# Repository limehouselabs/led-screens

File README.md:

# LED Screen Info

This repo runs [led.limehouselabs.org](https://led.limehouselabs.org) and also contains some additional info and assets.

To develop on the static site:
- Make sure submodules are initialised (`git submodule update --init`) to get the theme
- [install Hugo](https://gohugo.io/installation/) and run `hugo server` in this directory.

**To keep the repo size small, please do not add large software installers to this repo.** Upload them to the "Community Software" collection on archive.org and link them here.

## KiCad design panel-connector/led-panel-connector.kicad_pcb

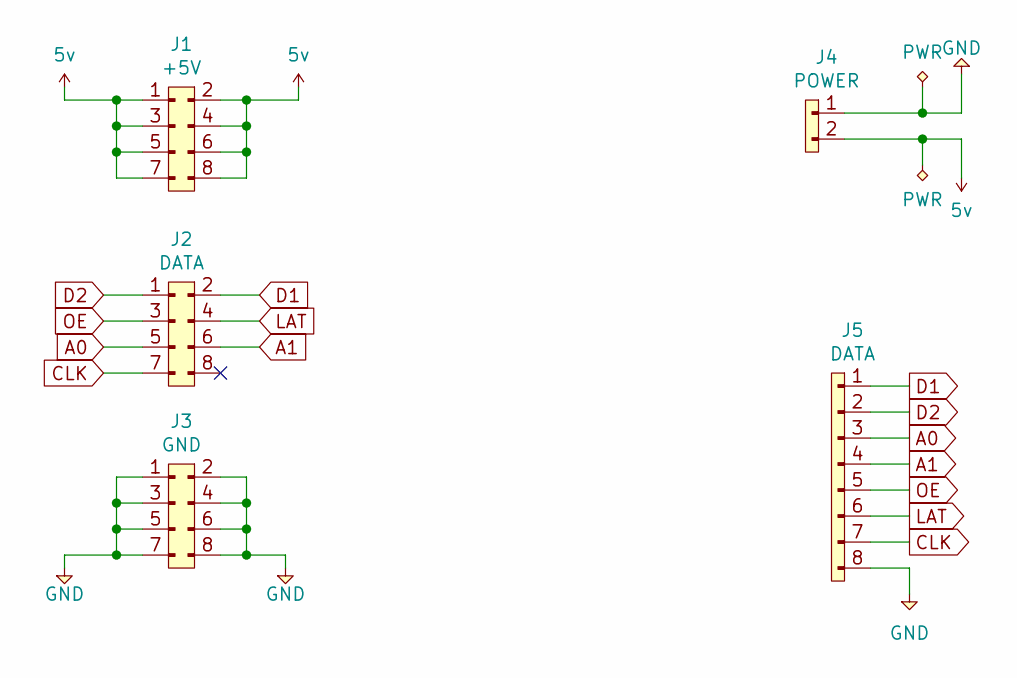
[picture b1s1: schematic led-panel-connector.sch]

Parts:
J1: +5V; PinSocket_2x04_P2.54mm_Vertical
J2: DATA; PinSocket_2x04_P2.54mm_Vertical
J3: GND; PinSocket_2x04_P2.54mm_Vertical
J4: POWER; JST_VH_B2P-VH_1x02_P3.96mm_Vertical
J5: DATA; JST_PH_S8B-PH-K_1x08_P2.00mm_Horizontal

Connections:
5v: J1.1, J1.2, J1.3, J1.4, J1.5, J1.6, J1.7, J1.8, J4.2
A0: J2.5, J5.3
A1: J2.6, J5.4
CLK: J2.7, J5.7
D1: J2.2, J5.1
D2: J2.1, J5.2
GND: J3.1, J3.2, J3.3, J3.4, J3.5, J3.6, J3.7, J3.8, J4.1, J5.8
LAT: J2.4, J5.6
OE: J2.3, J5.5

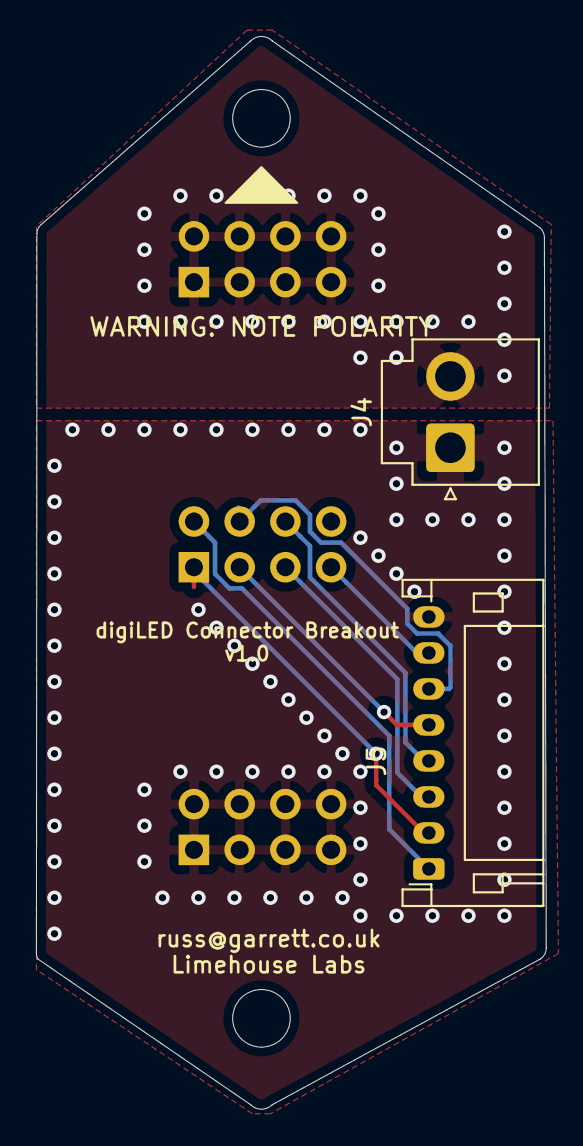
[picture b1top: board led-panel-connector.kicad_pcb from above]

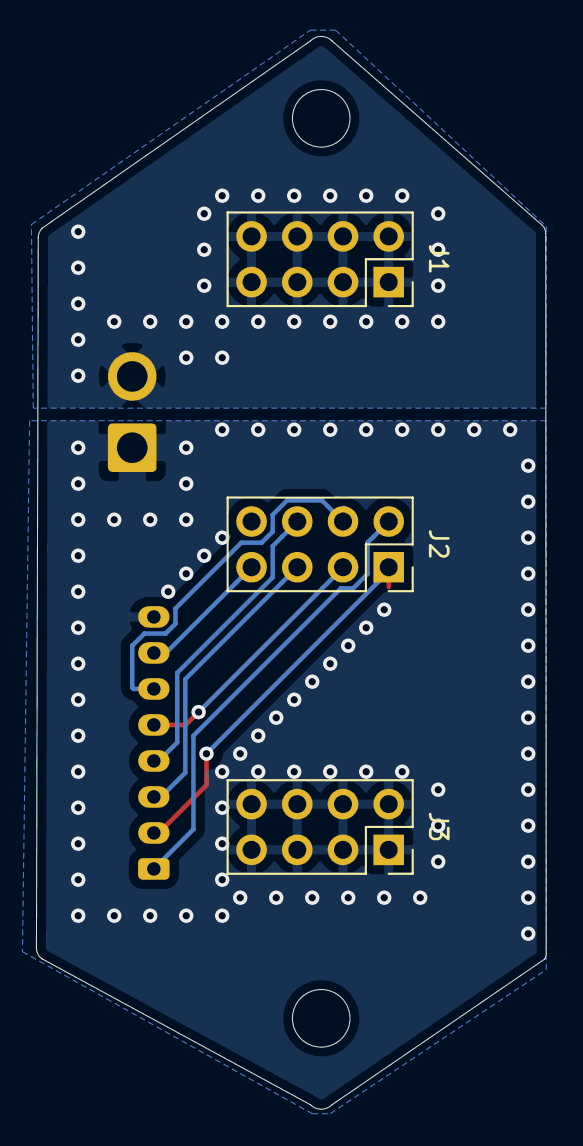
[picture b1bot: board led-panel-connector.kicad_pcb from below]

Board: 2 copper layers, 28.3 x 59.6 mm, 5 parts (3 on the bottom side), 9 nets.

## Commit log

2019-03-28 Initial connector version
2019-03-28 Add some stuff
2019-11-20 README update
2023-08-31 PDF and linked files of info on Hackspace wiki in case it disappears.
2023-09-14 hugo site for LED panel docs
2023-09-14 Add actions build
2023-09-14 Set theme
2023-09-15 Add more chips
2023-09-15 Add note about pin headers
2023-09-15 Bit more detail
2023-09-15 Add some info about the Stella screen
2023-09-15 Fix edit link
2023-09-16 Add photo and more info
2023-09-16 Various updates
2023-09-16 Add notes for DMG1083
2023-09-16 More notes
2023-09-16 Don't be too fancy with the pinouts
2023-09-16 Russssssssssssssssssss has to many sssssssssssssssssses
2023-09-17 Remove offer for the moment
2023-09-17 Add supply voltage
2023-09-17 Add more datasheets and info on DMG1083
2023-09-17 Add note about voltage
2023-09-17 Add nix flake
2023-09-18 Mention submodules in readme
2023-09-18 Add a bunch of extra info on chips and connections
2023-09-18 Add some more links
2023-09-18 Add power connectors
2023-09-18 Styling tweak
2023-09-19 Add power connector info
2023-10-05 Add some more detail on the DMG1083
2023-10-15 Add hypothesis about the SR line
2023-10-20 Add newer datasheet and application note for MBI5153
2023-10-20 Change note on scan line switching from updated AN
2023-11-18 DMG1083 updates
2024-01-09 Add link to ESP32 code
2024-01-18 KiCAD symbol for DMG1083
2024-01-18 Add missing pin, remove incorrect footprint ref
2024-05-12 Add flight case dimensions
2024-07-29 Update _index.md
    Update ESP32 implementation details
2024-09-08 Add some links
2025-01-01 Screens update
2025-01-01 Upgrade hugo
2025-01-02 Update _index.md
    tile size
2025-01-02 added photos from disassembly
2025-01-02 updated uri to subfolder
2025-01-02 added ffplay command
2025-01-02 added table header
2025-01-02 +1 floor panel
2025-01-02 Update _index.md
    described software configuration and how we broke it.
2025-01-03 LED floor updates
2025-01-03 Fix link to software, README update
2025-01-03 Fix config links
2025-08-29 Re-enable giveaway page
2025-12-12 Add MBI5050 datasheet
2025-12-13 Add docs for autumn 2025 screens
2025-12-13 Update deprecated action
2025-12-13 Update other actions
